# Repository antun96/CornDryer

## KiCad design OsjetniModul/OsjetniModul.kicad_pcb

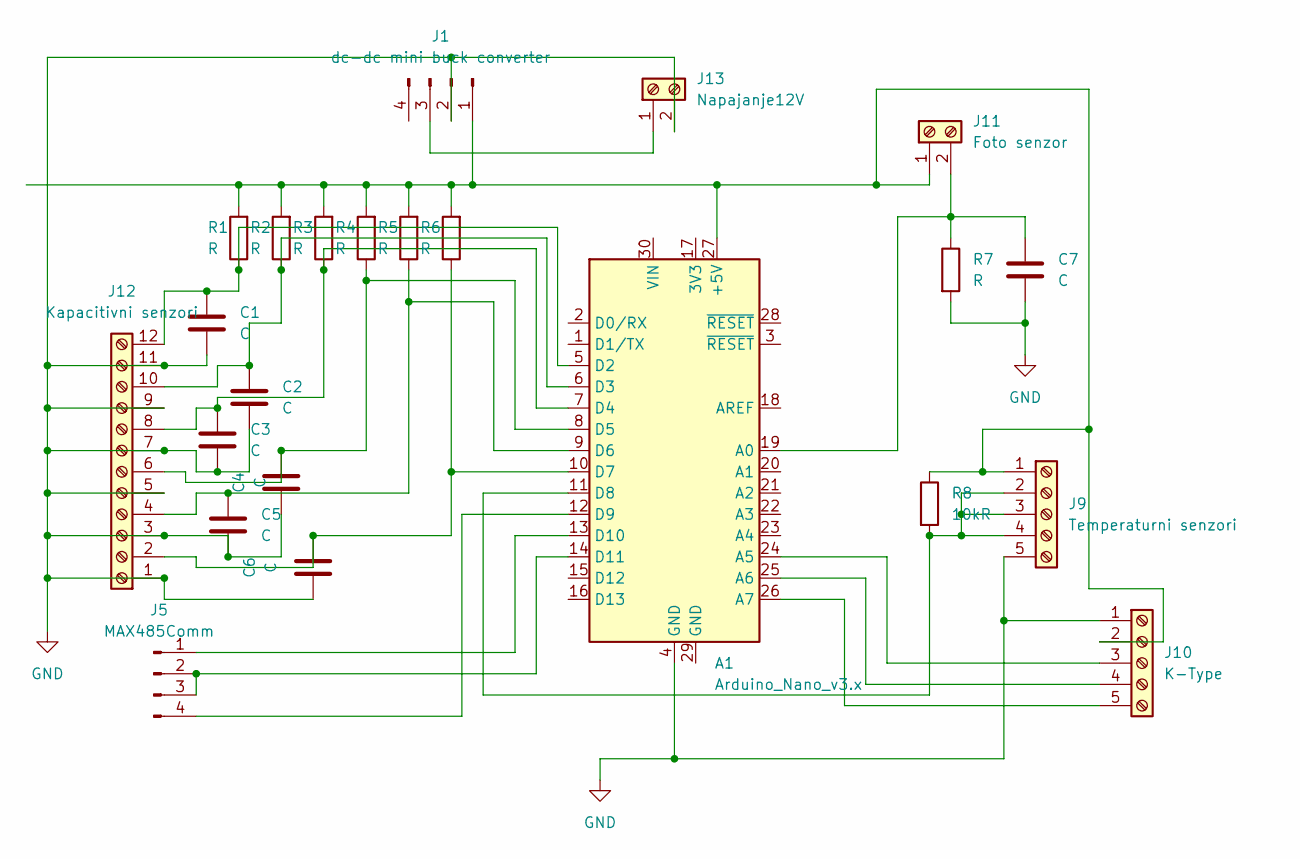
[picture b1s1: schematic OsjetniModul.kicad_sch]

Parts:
A1: Arduino_Nano_v3.x; Arduino_Nano
C1, C2, C3, C4, C5, C6, C7: C; CP_Radial_D5.0mm_P2.00mm
J1: dc-dc mini buck converter; PinHeader_1x04_P2.54mm_Vertical
J5: MAX485Comm; PinHeader_1x04_P2.54mm_Vertical
J9: Temperaturni senzori; TerminalBlock_Phoenix_MKDS-1,5-5_1x05_P5.00mm_Horizontal
J10: K-Type; TerminalBlock_Phoenix_MKDS-1,5-5_1x05_P5.00mm_Horizontal
J11: Foto senzor; TerminalBlock_Phoenix_MKDS-1,5-2_1x02_P5.00mm_Horizontal
J12: Kapacitivni senzori; TerminalBlock_Phoenix_MKDS-3-12-5.08_1x12_P5.08mm_Horizontal
J13: Napajanje12V; TerminalBlock_Phoenix_MKDS-1,5-2_1x02_P5.00mm_Horizontal
R1, R2, R3, R4, R5, R6, R7: R; R_Axial_DIN0207_L6.3mm_D2.5mm_P10.16mm_Horizontal
R8: 10kR; R_Axial_DIN0207_L6.3mm_D2.5mm_P10.16mm_Horizontal

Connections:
GND: A1.4 (GND), C1.1, C2.1, C3.1, C4.1, C5.1, C6.1, C7.2, J1.2, J9.5, J10.1, J12.1, J12.3, J12.5, J12.7, J12.9, J12.11, J13.2, R7.2
unnamed: A1.27 (+5V), J1.1, J9.1, J10.2, J11.1, R1.2, R2.2, R3.2, R4.2, R5.2, R6.2, R8.1
unnamed: A1.19 (A0), C7.1, J11.2, R7.1
unnamed: A1.24 (A5), J10.3
unnamed: A1.25 (A6), J10.4
unnamed: A1.26 (A7), J10.5
unnamed: A1.5 (D2), C1.2, J12.12, R1.1
unnamed: A1.6 (D3), C2.2, J12.10, R2.1
unnamed: A1.7 (D4), C3.2, J12.8, R3.1
unnamed: A1.8 (D5), C4.2, J12.6, R4.1
unnamed: A1.9 (D6), C5.2, J12.4, R5.1
unnamed: A1.10 (D7), C6.2, J12.2, R6.1
unnamed: A1.11 (D8), J9.2, J9.3, J9.4, R8.2
unnamed: A1.12 (D9), J5.4
unnamed: A1.13 (D10), J5.1
unnamed: A1.14 (D11), J5.2, J5.3
unnamed: J1.3, J13.1

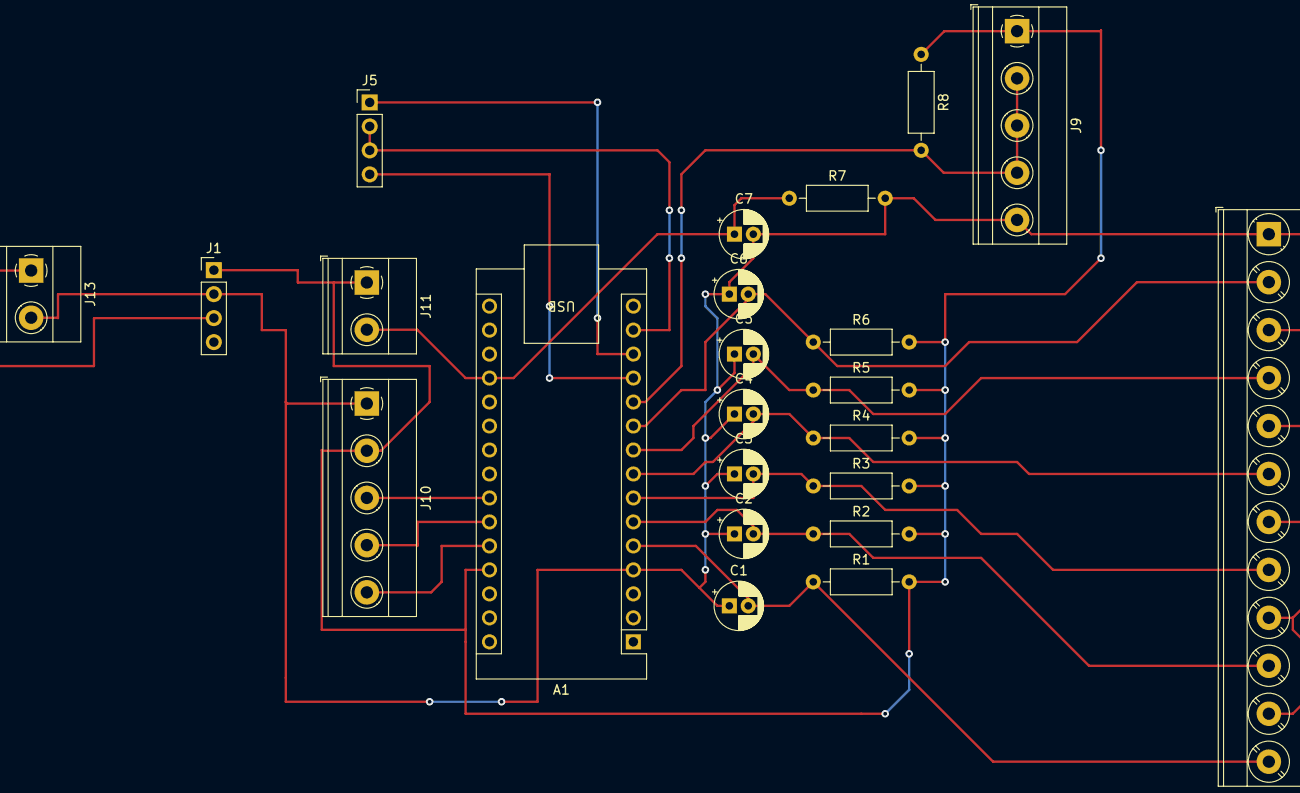
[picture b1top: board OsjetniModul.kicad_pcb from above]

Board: 2 copper layers, 23 parts (0 on the bottom side), 17 nets.

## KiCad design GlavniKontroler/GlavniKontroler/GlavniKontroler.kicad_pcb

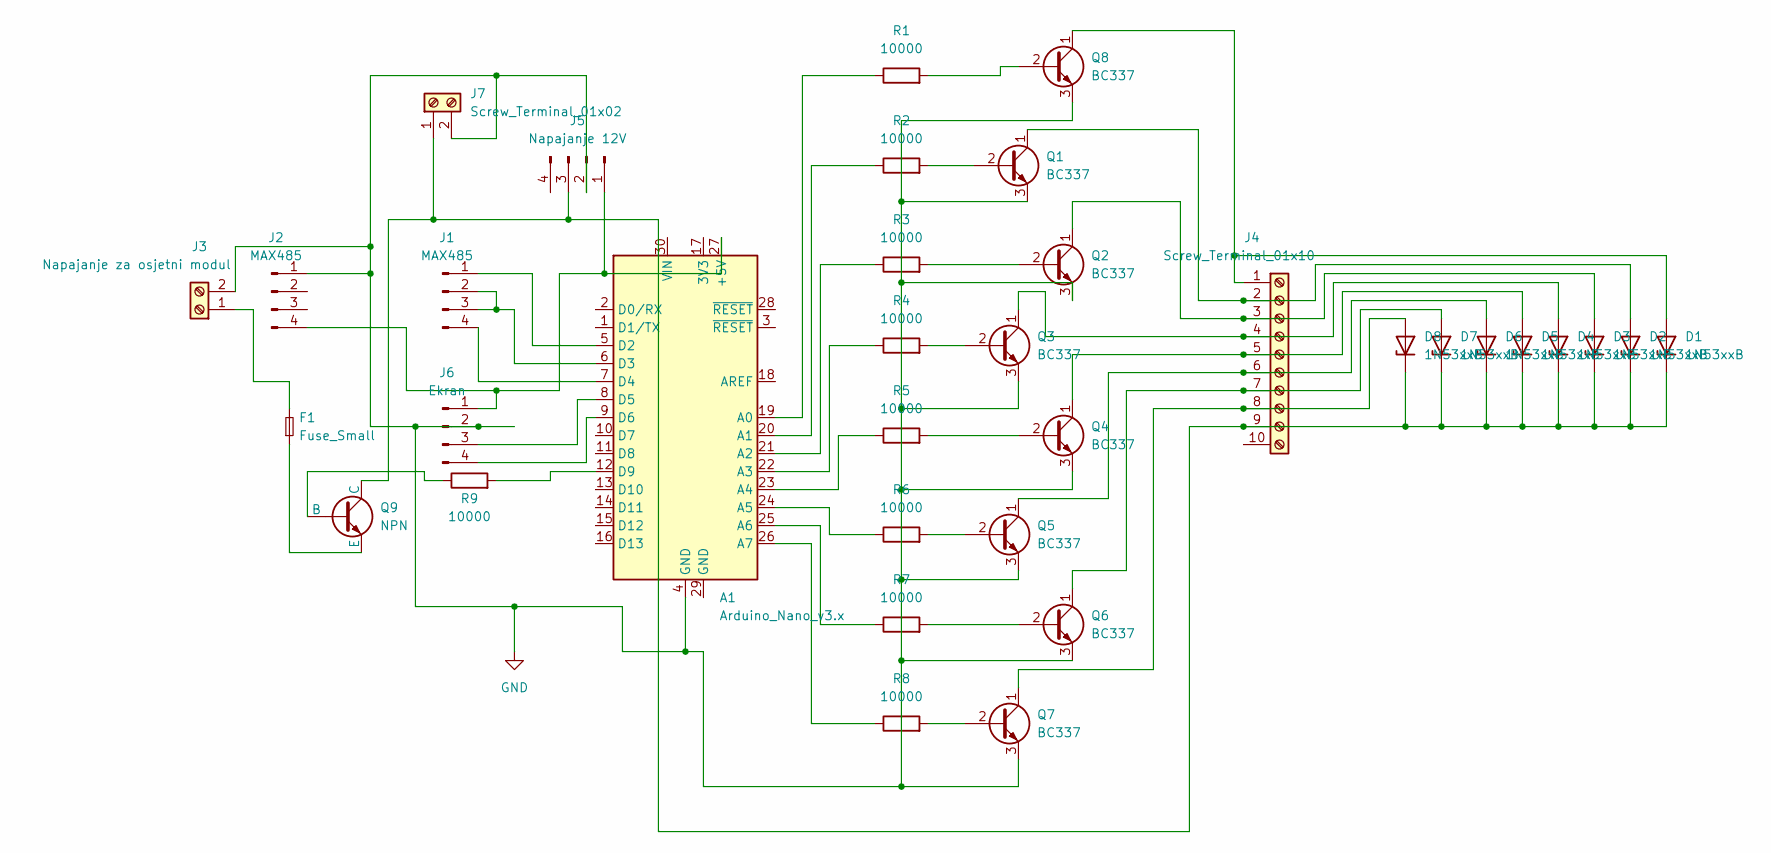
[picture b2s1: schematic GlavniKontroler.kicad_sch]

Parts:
A1: Arduino_Nano_v3.x; Arduino_Nano
D1, D2, D3, D4, D5, D6, D7, D8: 1N53xxB; D_DO-15_P10.16mm_Horizontal
F1: Fuse_Small; Fuseholder_Clip-5x20mm_Littelfuse_111_Inline_P20.00x5.00mm_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
J1, J2: MAX485; PinHeader_1x04_P2.54mm_Vertical
J3: Napajanje za osjetni modul; TerminalBlock_Phoenix_MKDS-1,5-2_1x02_P5.00mm_Horizontal
J4: Screw_Terminal_01x10; TerminalBlock_Phoenix_MKDS-1,5-10_1x10_P5.00mm_Horizontal
J5: Napajanje 12V; PinHeader_1x04_P2.54mm_Vertical
J6: Ekran; PinHeader_1x04_P2.54mm_Vertical
J7: Screw_Terminal_01x02; TerminalBlock_Phoenix_MKDS-1,5-2-5.08_1x02_P5.08mm_Horizont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
Q1, Q2, Q3, Q4, Q5, Q6, Q7, Q8: BC337; TO-92_Inline
Q9: NPN; TO-92_Inline
R1, R2, R3, R4, R5, R6, R7, R8, R9: 10000; R_Axial_DIN0207_L6.3mm_D2.5mm_P10.16mm_Horizontal

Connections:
GND: A1.4 (GND), J2.1, J3.2, J5.2, J6.2, J7.2, Q1.3 (E), Q2.3 (E), Q3.3 (E), Q4.3 (E), Q5.3 (E), Q6.3 (E), Q7.3 (E), Q8.3 (E)
unnamed: A1.27 (+5V), J2.4, J5.1, J6.1
unnamed: A1.19 (A0), R1.1
unnamed: A1.20 (A1), R2.1
unnamed: A1.21 (A2), R3.1
unnamed: A1.22 (A3), R4.1
unnamed: A1.23 (A4), R5.1
unnamed: A1.24 (A5), R6.1
unnamed: A1.25 (A6), R7.1
unnamed: A1.26 (A7), R8.1
unnamed: A1.5 (D2), J1.1
unnamed: A1.6 (D3), J1.2, J1.3
unnamed: A1.7 (D4), J1.4
unnamed: A1.8 (D5), J6.3
unnamed: A1.9 (D6), J6.4
unnamed: A1.12 (D9), R9.2
unnamed: D1.2 (A), J4.1, Q8.1 (C)
unnamed: D1.1 (K), D2.1 (K), D3.1 (K), D4.1 (K), D5.1 (K), D6.1 (K), D7.1 (K), D8.1 (K), J4.9, J5.3, J7.1, Q9.1 (C)
unnamed: D2.2 (A), J4.2, Q1.1 (C)
unnamed: D3.2 (A), J4.3, Q2.1 (C)
unnamed: D4.2 (A), J4.4, Q3.1 (C)
unnamed: D5.2 (A), J4.5, Q4.1 (C)
unnamed: D6.2 (A), J4.6, Q5.1 (C)
unnamed: D7.2 (A), J4.7, Q6.1 (C)
unnamed: D8.2 (A), J4.8, Q7.1 (C)
unnamed: F1.2, J3.1
unnamed: Q1.2 (B), R2.2
unnamed: Q2.2 (B), R3.2
unnamed: Q3.2 (B), R4.2
unnamed: Q4.2 (B), R5.2
unnamed: Q5.2 (B), R6.2
unnamed: Q6.2 (B), R7.2
unnamed: Q7.2 (B), R8.2
unnamed: Q8.2 (B), R1.2
unnamed: Q9.2 (B), R9.1
unnamed: F1.1, Q9.3 (E)

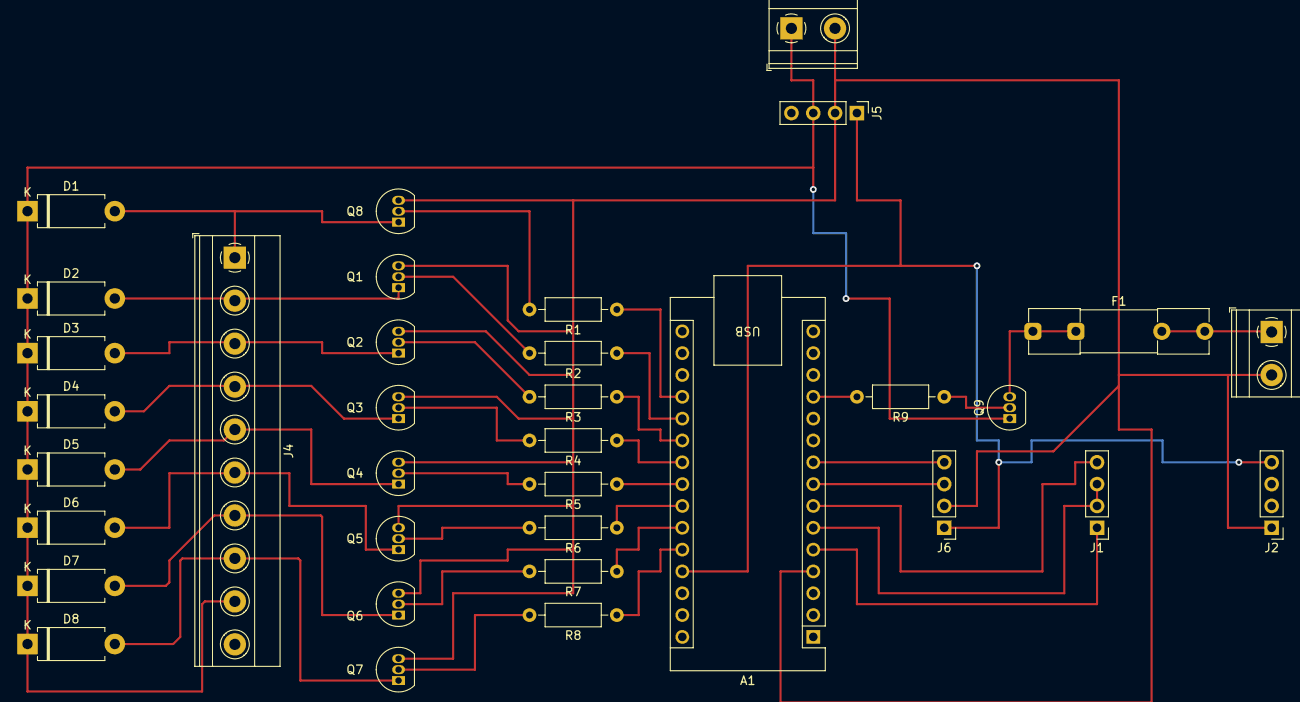
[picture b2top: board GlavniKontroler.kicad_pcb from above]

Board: 2 copper layers, 35 parts (0 on the bottom side), 36 nets.

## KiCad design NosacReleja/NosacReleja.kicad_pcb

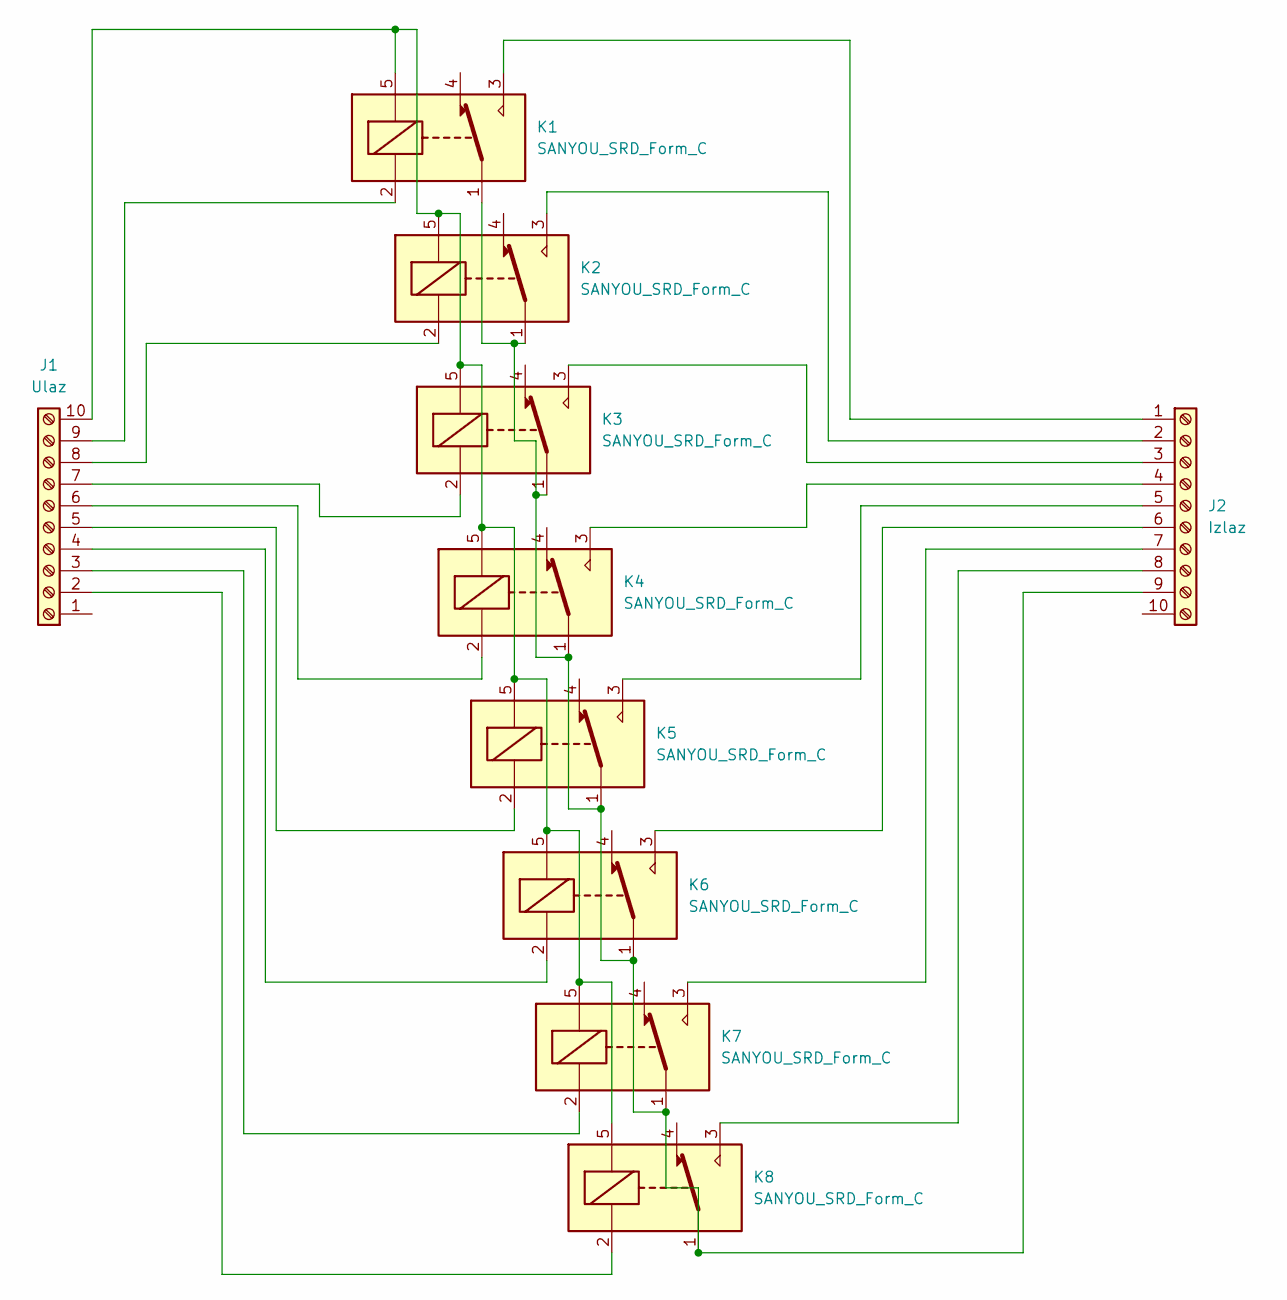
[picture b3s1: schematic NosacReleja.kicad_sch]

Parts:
J1: Ulaz; TerminalBlock_Phoenix_MKDS-1,5-10_1x10_P5.00mm_Horizontal
J2: Izlaz; TerminalBlock_Phoenix_MKDS-1,5-10_1x10_P5.00mm_Horizontal
K1, K2, K3, K4, K5, K6, K7, K8: SANYOU_SRD_Form_C; Relay_SPDT_SANYOU_SRD_Series_Form_C

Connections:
unnamed: J1.2, K8.2
unnamed: J1.3, K7.2
unnamed: J1.4, K6.2
unnamed: J1.5, K5.2
unnamed: J1.6, K4.2
unnamed: J1.7, K3.2
unnamed: J1.8, K2.2
unnamed: J1.9, K1.2
unnamed: J1.10, K1.5, K2.5, K3.5, K4.5, K5.5, K6.5, K7.5, K8.5
unnamed: J2.1, K1.3
unnamed: J2.2, K2.3
unnamed: J2.3, K3.3
unnamed: J2.4, K4.3
unnamed: J2.5, K5.3
unnamed: J2.6, K6.3
unnamed: J2.7, K7.3
unnamed: J2.8, K8.3
unnamed: J2.9, K1.1, K2.1, K3.1, K4.1, K5.1, K6.1, K7.1, K8.1

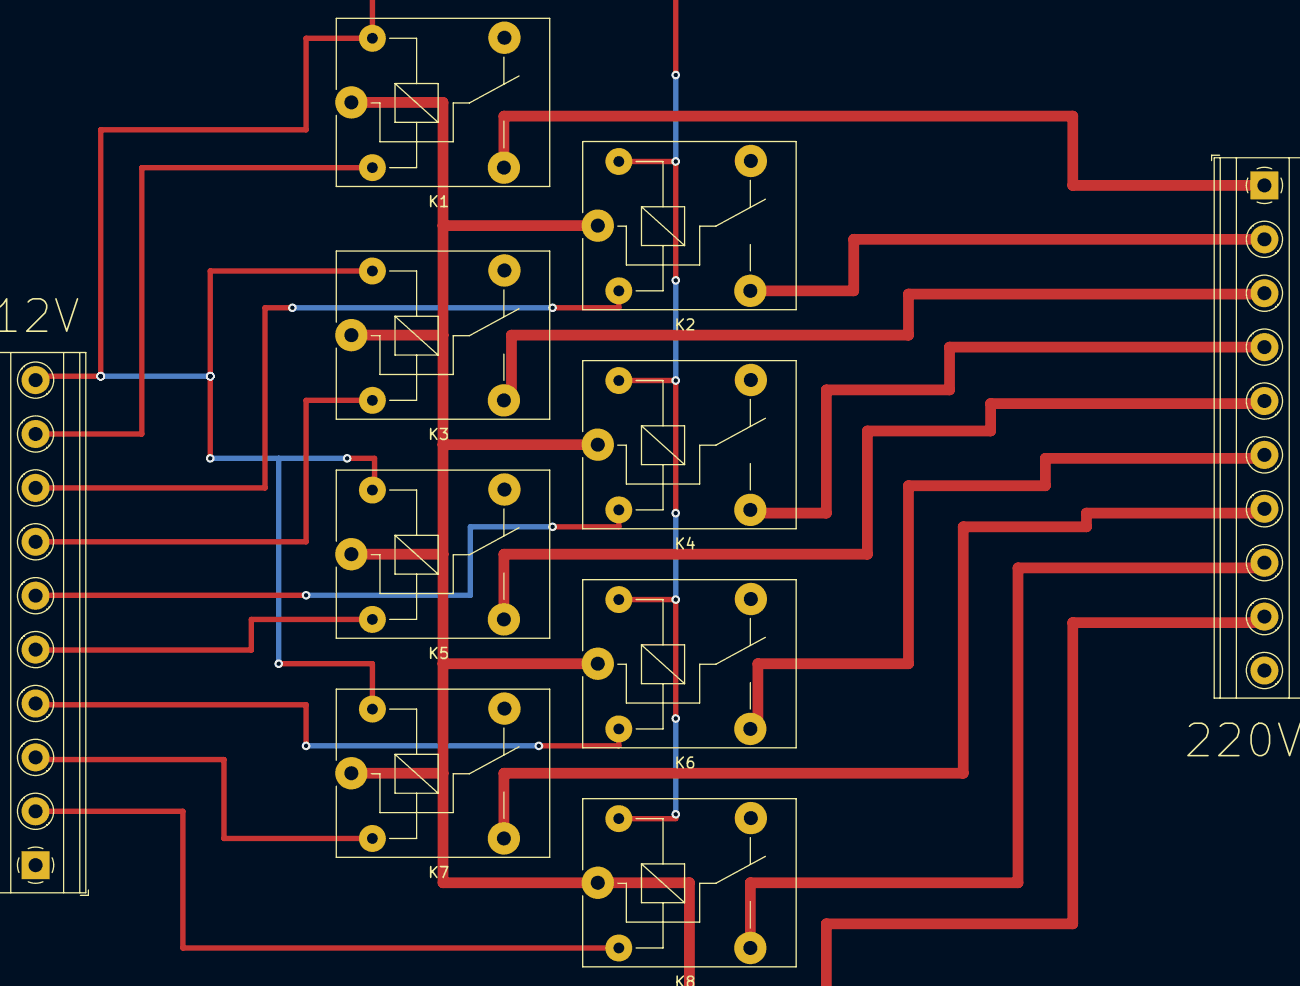
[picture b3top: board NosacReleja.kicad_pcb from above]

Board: 2 copper layers, 10 parts (0 on the bottom side), 18 nets.

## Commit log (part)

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2024-12-31 osjetni modul initial commit
2025-01-01 declared pins for sensing module
2025-01-06 added libraries and some methods to code
2025-01-16 added code to read serial,
2025-01-20 added communication methods to be able to communicate with slave
2025-01-20 added pins for nextion and serial communicator object
2025-01-21 added design
2025-01-23 added better ux design
2025-01-29 added start of drying process
2025-02-05 made some changes, removed stupid methods, still need to get minimum and maximum from rom, store it in 2 separe bytes
2025-02-12 added one more cap sensor to pictures in code added logic for shutdown, empty half and empty full, also added signalization of error and end of process
2025-02-14 added methods to update screen, still need buttons to configure
2025-02-17 added eeprom functionalities, buttons for commands
2025-02-17 added commands to buttons
2025-02-18 added aditional checks
2025-02-23 updates parameters on screen only if first time showing or there is a change in one variable, added another page for removing blockage for corn to pass from drying chamber to cooling chamber, updated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
2025-02-23 main.cpp now bulds
